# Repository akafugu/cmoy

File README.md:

cmoy
====

Eagle Design files for our cmoy headphone amplifier.

License: Creative Commons Attribution/Share-Alike.

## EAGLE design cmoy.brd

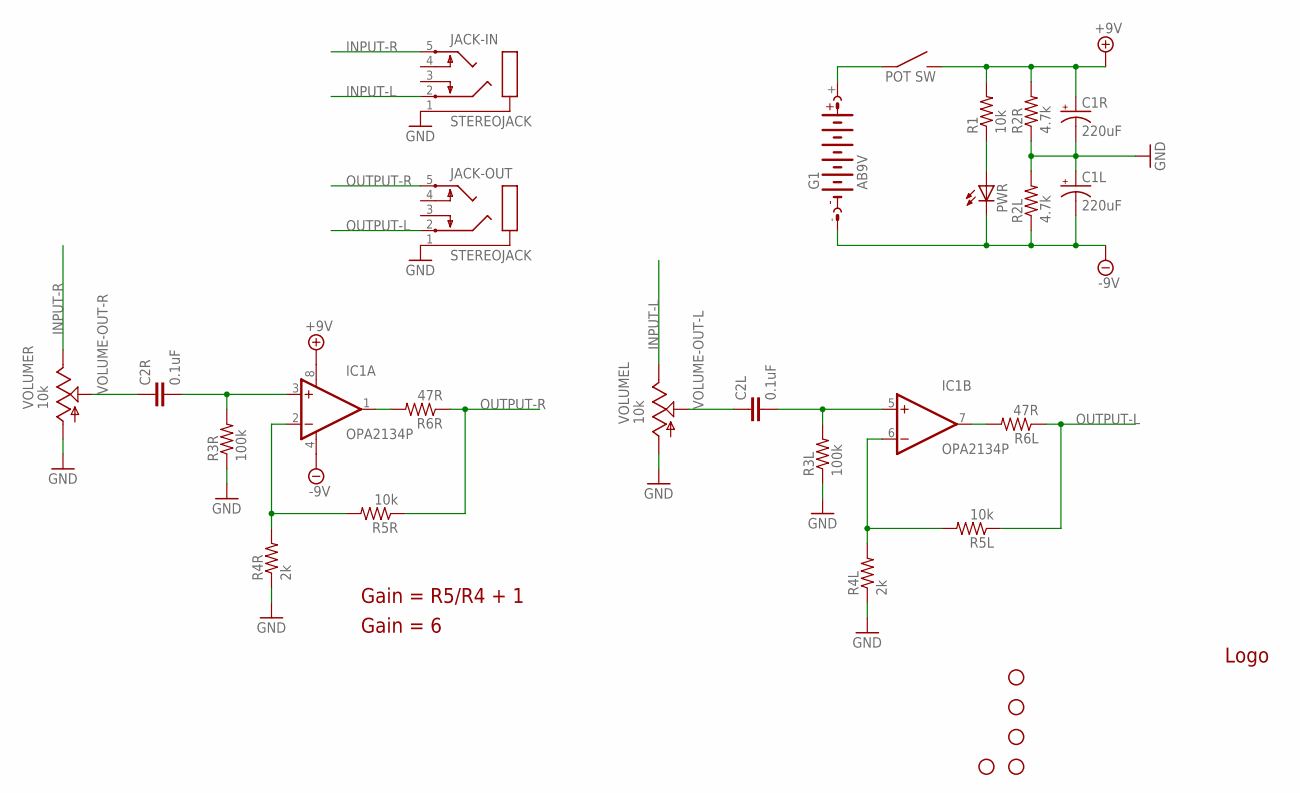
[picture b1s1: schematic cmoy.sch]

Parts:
C1L, C1R: 220uF; CPOL-RADIAL-6.3MM
C2L, C2R: 0.1uF; CAP-PTH-VIMA-MKS2C031001A00KSSD
G1: AB9V
IC1: OPA2134P; DIL-8
JACK-IN: STEREOJACK; STX3100
JACK-OUT: STEREOJACK; STX3100
JP1, JP2, JP3, JP4, JP5: STAND-OFF
PWR: LED-3MM-MINUS; LED3MM-MINUS
R1: 10k; 1/6W-RES-OUTLINE
R2L, R2R: 4.7k; 1/6W-RES-OUTLINE
R3L, R3R: 100k; 1/4W-RES-OUTLINE
R4L, R4R: 2k; 1/4W-RES-OUTLINE
R5L, R5R: 10k; 1/4W-RES-OUTLINE
R6L, R6R: 47R; 1/4W-RES-OUTLINE
U$1: OSHW-LOGO-OUTLINE
VOLUME: 10k; ALPS_RK0971221Z0X

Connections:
+9V: C1R.1 (+), IC1.8 (V+), R1.2, R2R.2, VOLUME.S2
-9V: C1L.2 (-), G1.-, IC1.4 (V-), PWR.K (C), R2L.1
GND: C1L.1 (+), C1R.2 (-), JACK-IN.1, JACK-OUT.1, R2L.2, R2R.1, R3L.P$1 (1), R3R.P$1 (1), R4L.P$1 (1), R4R.P$1 (1), VOLUME.G1 (1), VOLUME.G2 (1)
INPUT-L: JACK-IN.2, VOLUME.I1 (3)
INPUT-R: JACK-IN.5, VOLUME.I2 (3)
L+: C2L.2, IC1.5 (+IN), R3L.P$2 (2)
L-: IC1.6 (-IN), R4L.P$2 (2), R5L.P$2 (2)
unnamed: PWR.A, R1.1
unnamed: G1.+, VOLUME.S1
OP-L: IC1.7 (OUT), R6L.P$2 (2)
OP-R: IC1.1 (OUT), R6R.P$2 (2)
OUTPUT-L: JACK-OUT.2, R5L.P$1 (1), R6L.P$1 (1)
OUTPUT-R: JACK-OUT.5, R5R.P$1 (1), R6R.P$1 (1)
R+: C2R.2, IC1.3 (+IN), R3R.P$2 (2)
R-: IC1.2 (-IN), R4R.P$2 (2), R5R.P$2 (2)
VOLUME-OUT-L: C2L.1, VOLUME.O1 (2)
VOLUME-OUT-R: C2R.1, VOLUME.O2 (2)

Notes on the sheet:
Gain = R5/R4 + 1
Gain = 6

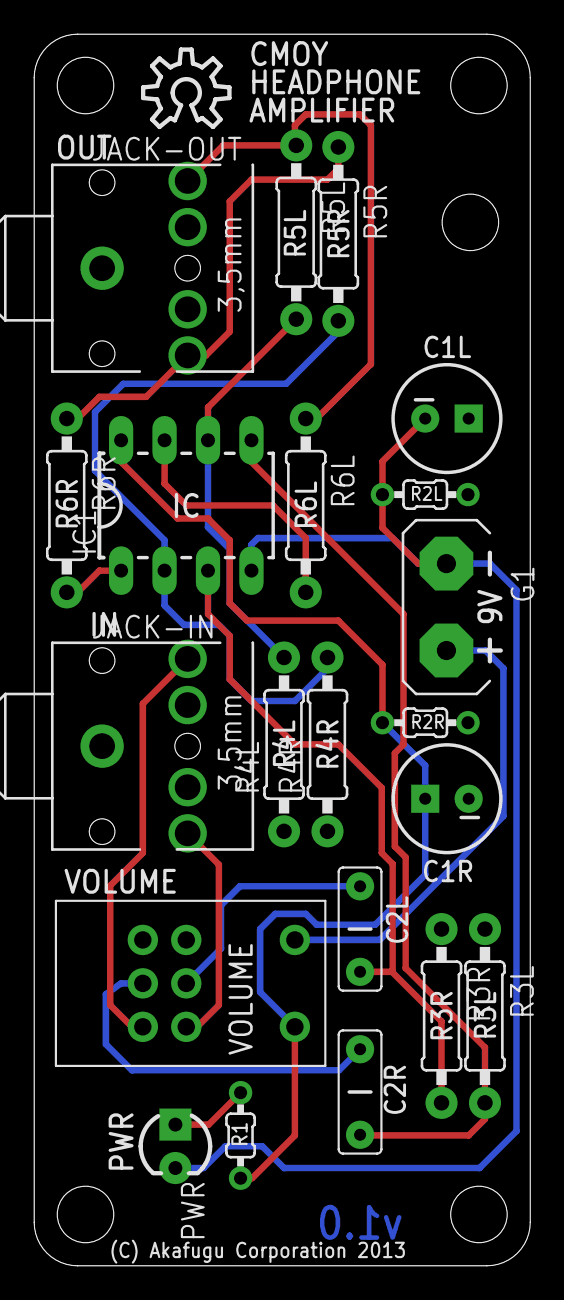
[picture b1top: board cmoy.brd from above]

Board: 2 copper layers, 29.0 x 72.0 mm, 27 parts (0 on the bottom side), 17 nets.

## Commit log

2013-09-04 Akafugu cmoy headphone amplifier, reference design, v1.0
2013-10-12 Added png of schematic
2014-04-11 Added license
